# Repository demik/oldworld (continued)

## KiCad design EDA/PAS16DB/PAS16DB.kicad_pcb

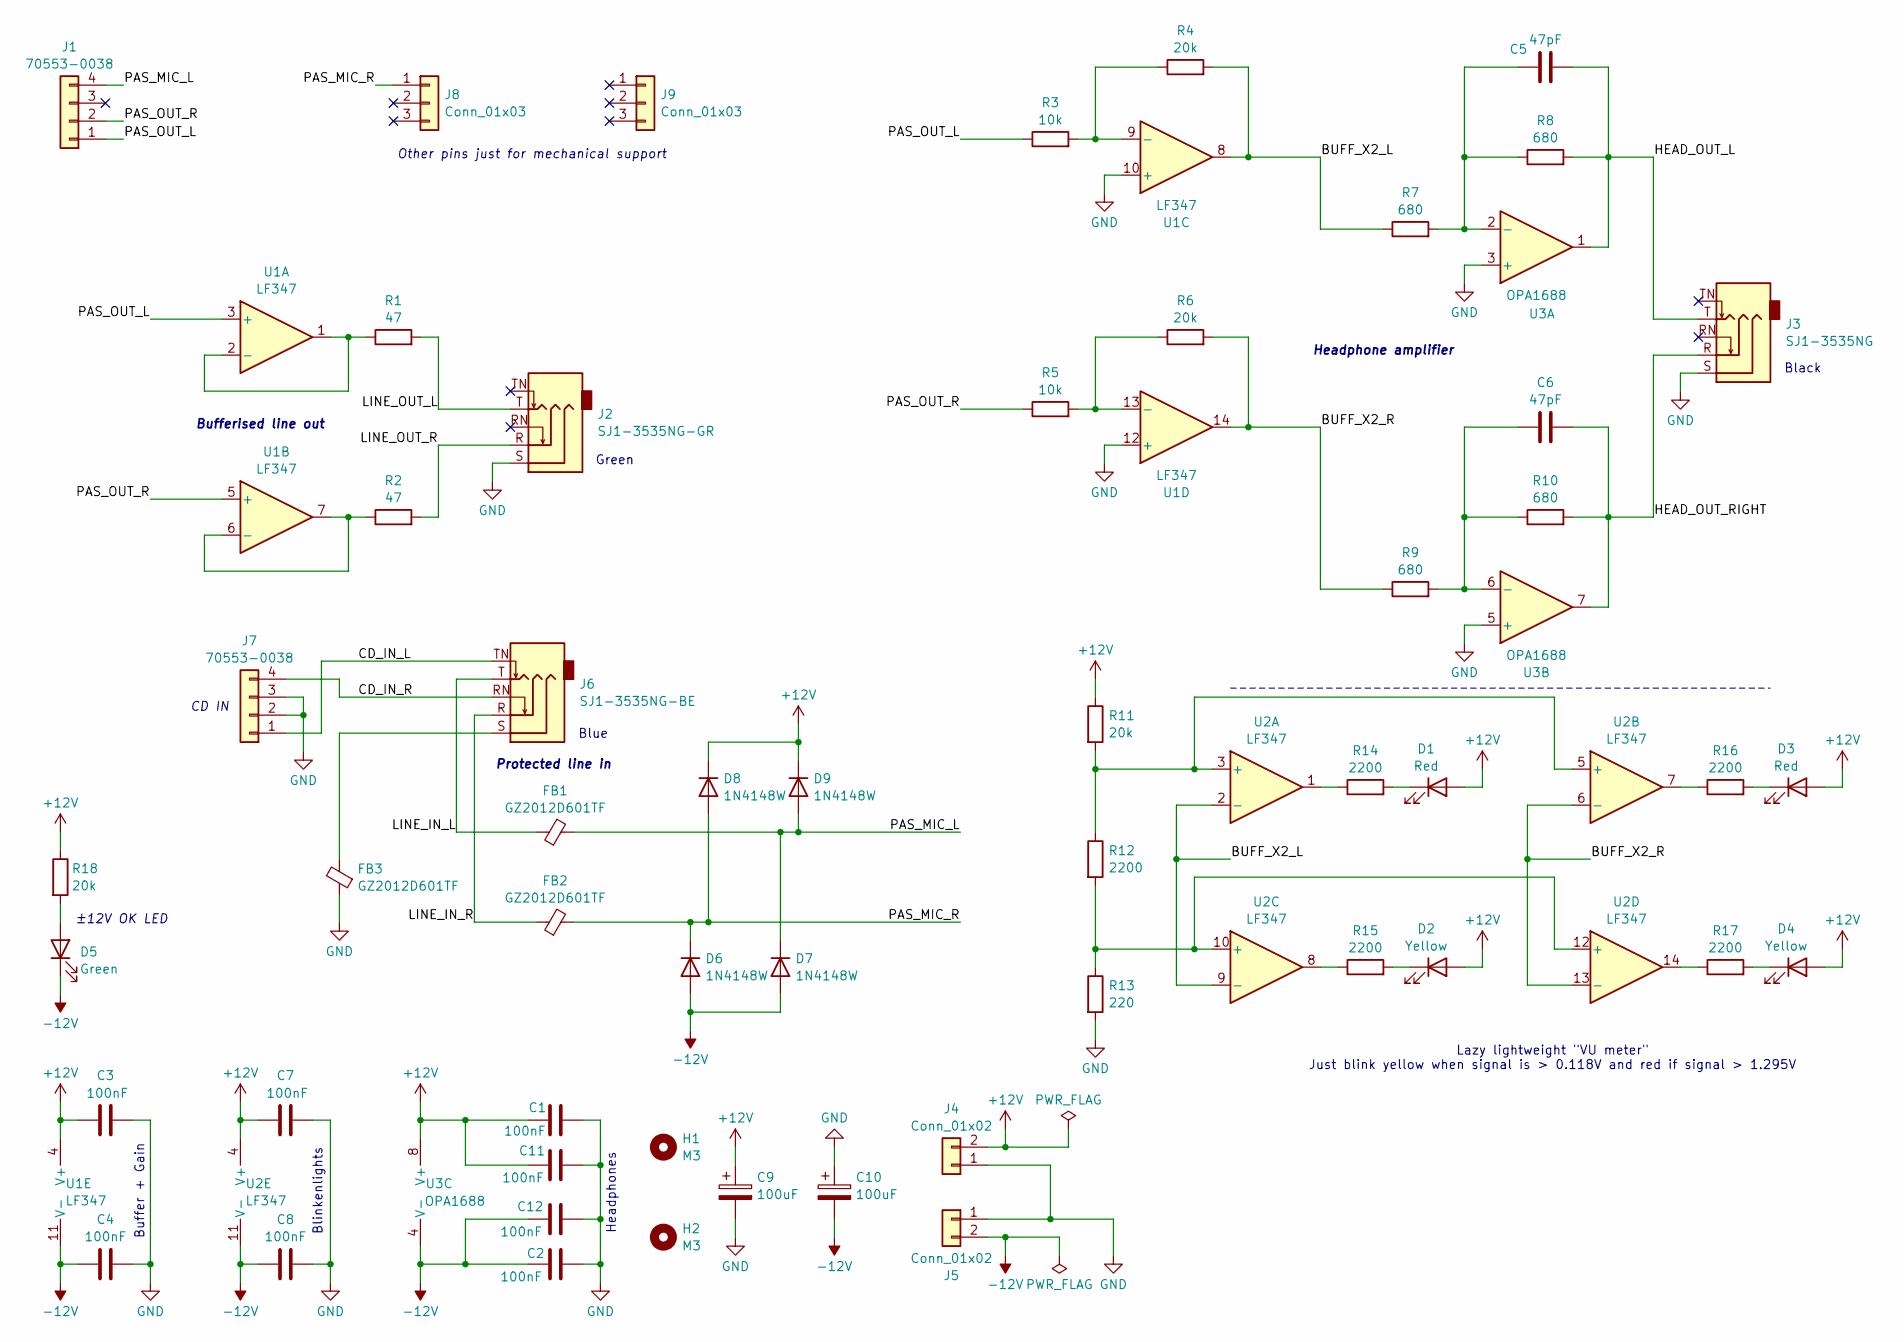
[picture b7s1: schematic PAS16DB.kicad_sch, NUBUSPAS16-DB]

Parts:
C1, C2, C3, C4, C7, C8, C11, C12: 100nF; C_0805_2012Metric; LCSC Part # C49678
C5, C6: 47pF; C_0805_2012Metric; LCSC Part # C14857
C9, C10: 100uF; CP_Axial_L11.0mm_D8.0mm_P15.00mm_Horizontal
D1, D3: Red; LED_0805_2012Metric; LCSC Part # C84256
D2, D4: Yellow; LED_0805_2012Metric; LCSC Part # C2296
D5: Green; LED_0805_2012Metric; LCSC Part # C2297
D6, D7, D8, D9: 1N4148W; D_SOD-123; LCSC Part # C81598
FB1, FB2, FB3: GZ2012D601TF; L_0805_2012Metric; LCSC Part # C1017
H1, H2: M3; MountingHole_3.2mm_M3
J1, J7: 70553-0038; 0705530003; LCSC Part # C564148
J2: SJ1-3535NG-GR; Jack_3.5mm_CUI_SJ1-3535NG_Horizontal; LCSC Part # C4992036
J3: SJ1-3535NG; Jack_3.5mm_CUI_SJ1-3535NG_Horizontal; LCSC Part # C4991610
J4, J5: Conn_01x02; PinHeader_1x02_P2.54mm_Vertical
J6: SJ1-3535NG-BE; Jack_3.5mm_CUI_SJ1-3535NG_Horizontal
J8, J9: Conn_01x03; PinHeader_1x03_P2.54mm_Vertical
R1, R2: 47; R_0805_2012Metric; LCSC Part # C17714
R3, R5: 10k; R_0805_2012Metric; LCSC Part # C17414
R4, R6, R11, R18: 20k; R_0805_2012Metric; LCSC Part # C4328
R7, R8, R9, R10: 680; R_0805_2012Metric; LCSC Part # C17798
R12, R14, R15, R16, R17: 2200; R_0805_2012Metric; LCSC Part # C17520
R13: 220; R_0805_2012Metric; LCSC Part # C17557
U1, U2: LF347; SOIC-14_3.9x8.7mm_P1.27mm; LCSC Part # C283322
U3: OPA1688; SOIC-8_3.9x4.9mm_P1.27mm; LCSC Part # C544851

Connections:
+12V: C1.1, C3.1, C7.1, C9.1, C11.1, D1.2 (A), D2.2 (A), D3.2 (A), D4.2 (A), D8.1 (K), D9.1 (K), J4.2, R11.1, R18.1, U1.4 (V+), U2.4 (V+), U3.8 (V+)
-12V: C2.1, C4.1, C8.1, C10.2, C12.1, D5.1 (K), D6.2 (A), D7.2 (A), J5.2, U1.11 (V-), U2.11 (V-), U3.4 (V-)
/BUFF_X2_L: R4.2, R7.1, U1.8, U2.2 (-), U2.9 (-)
/BUFF_X2_R: R6.2, R9.1, U1.14, U2.6 (-), U2.13 (-)
/CD_IN_L: J6.TN, J7.1
/CD_IN_R: J6.RN, J7.4
/HEAD_OUT_L: C5.2, J3.T, R8.2, U3.1
/HEAD_OUT_RIGHT: C6.2, J3.R, R10.2, U3.7
/LINE_IN_L: FB1.1, J6.T
/LINE_IN_R: FB2.1, J6.R
/LINE_OUT_L: J2.T, R1.2
/LINE_OUT_R: J2.R, R2.2
/PAS_MIC_L: D7.1 (K), D9.2 (A), FB1.2, J1.4
/PAS_MIC_R: D6.1 (K), D8.2 (A), FB2.2, J8.1
/PAS_OUT_L: J1.1, R3.1, U1.3 (+)
/PAS_OUT_R: J1.2, R5.1, U1.5 (+)
GND: C1.2, C2.2, C3.2, C4.2, C7.2, C8.2, C9.2, C10.1, C11.2, C12.2, FB3.1, J2.S, J3.S, J4.1, J5.1, J7.2, J7.3, R13.2, U1.10 (+), U1.12 (+), U3.3 (+), U3.5 (+)
unnamed: D1.1 (K), R14.2
unnamed: D2.1 (K), R15.2
unnamed: D3.1 (K), R16.2
unnamed: D4.1 (K), R17.2
unnamed: D5.2 (A), R18.2
unnamed: FB3.2, J6.S
unnamed: R14.1, U2.1
unnamed: R15.1, U2.8
unnamed: R16.1, U2.7
unnamed: R17.1, U2.14
unnamed: R1.1, U1.1, U1.2 (-)
unnamed: R2.1, U1.6 (-), U1.7
unnamed: R3.2, R4.1, U1.9 (-)
unnamed: R5.2, R6.1, U1.13 (-)
unnamed: R11.2, R12.1, U2.3 (+), U2.5 (+)
unnamed: R12.2, R13.1, U2.10 (+), U2.12 (+)
unnamed: C5.1, R7.2, R8.1, U3.2 (-)
unnamed: C6.1, R9.2, R10.1, U3.6 (-)

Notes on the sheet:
±12V OK LED
Black
Bufferised line out
Other pins just for mechanical support
Headphones
Lazy lightweight "VU meter" Just blink yellow when signal is > 0.118V and red if signal > 1.295V
Headphone amplifier
CD IN
Protected line in
Green
Blinkenlights
Blue
Buffer + Gain

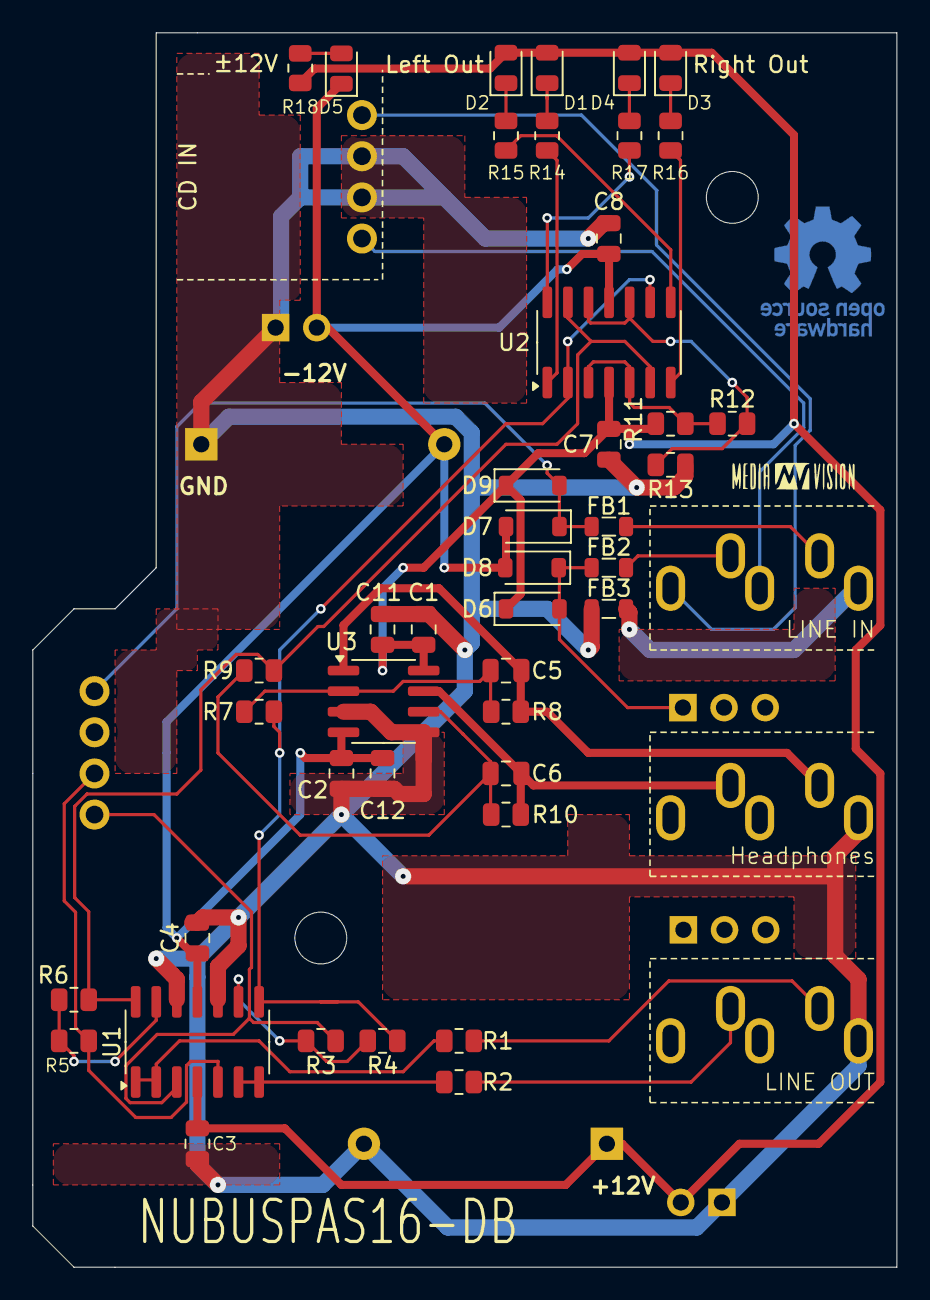
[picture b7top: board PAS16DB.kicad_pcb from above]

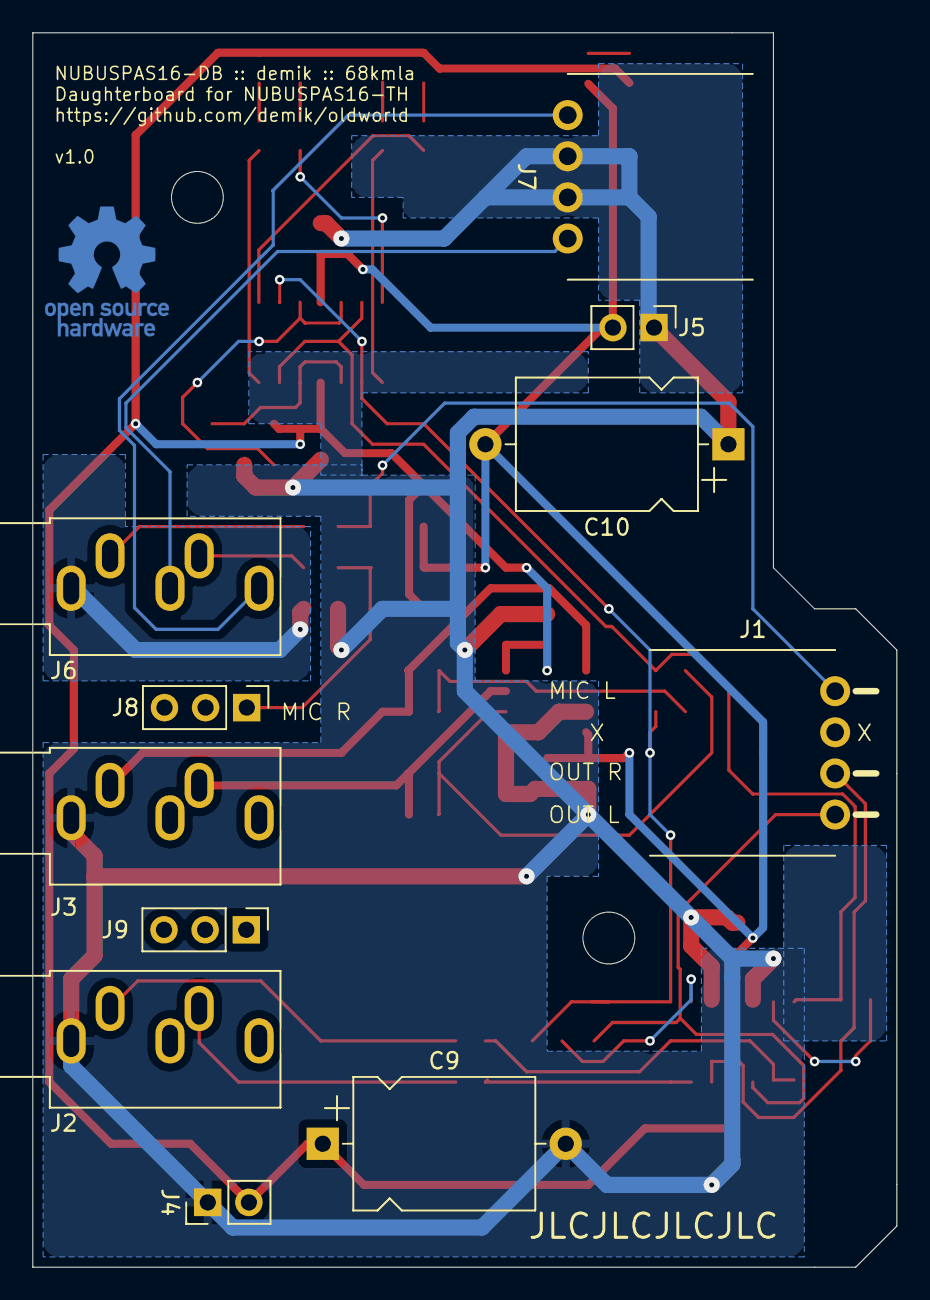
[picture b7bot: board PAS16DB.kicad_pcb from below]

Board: 2 copper layers, 53.3 x 76.2 mm, 56 parts (11 on the bottom side), 35 nets.

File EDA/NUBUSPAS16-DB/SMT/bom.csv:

Designator,Footprint,Quantity,Value,LCSC Part #
C1,0805,1,100nF,<pcbnew.PCB_FIELD; proxy of <Swig Object of type 'PCB_FIELD *' at 0x125257690> >
C10,CP_Axial_L11.0mm_D8.0mm_P15.00mm_Horizontal,1,100uF,<pcbnew.PCB_FIELD; proxy of <Swig Object of type 'PCB_FIELD *' at 0x124cc8b70> >
C11,0805,1,100nF,<pcbnew.PCB_FIELD; proxy of <Swig Object of type 'PCB_FIELD *' at 0x124cc8450> >
C12,0805,1,100nF,<pcbnew.PCB_FIELD; proxy of <Swig Object of type 'PCB_FIELD *' at 0x124cc8180> >
C2,0805,1,100nF,<pcbnew.PCB_FIELD; proxy of <Swig Object of type 'PCB_FIELD *' at 0x124cc8840> >
C3,0805,1,100nF,<pcbnew.PCB_FIELD; proxy of <Swig Object of type 'PCB_FIELD *' at 0x124c71570> >
C4,0805,1,100nF,<pcbnew.PCB_FIELD; proxy of <Swig Object of type 'PCB_FIELD *' at 0x124c71660> >
C5,0805,1,47pF,<pcbnew.PCB_FIELD; proxy of <Swig Object of type 'PCB_FIELD *' at 0x124c71f30> >
C6,0805,1,47pF,<pcbnew.PCB_FIELD; proxy of <Swig Object of type 'PCB_FIELD *' at 0x124c71bd0> >
C7,0805,1,100nF,<pcbnew.PCB_FIELD; proxy of <Swig Object of type 'PCB_FIELD *' at 0x124c71ba0> >
C8,0805,1,100nF,<pcbnew.PCB_FIELD; proxy of <Swig Object of type 'PCB_FIELD *' at 0x124c71a50> >
C9,CP_Axial_L11.0mm_D8.0mm_P15.00mm_Horizontal,1,100uF,<pcbnew.PCB_FIELD; proxy of <Swig Object of type 'PCB_FIELD *' at 0x124c71a20> >
D1,0805,1,Red,<pcbnew.PCB_FIELD; proxy of <Swig Object of type 'PCB_FIELD *' at 0x124c71420> >
D2,0805,1,Yellow,<pcbnew.PCB_FIELD; proxy of <Swig Object of type 'PCB_FIELD *' at 0x124c71b40> >
D3,0805,1,Red,<pcbnew.PCB_FIELD; proxy of <Swig Object of type 'PCB_FIELD *' at 0x124c71630> >
D4,0805,1,Yellow,<pcbnew.PCB_FIELD; proxy of <Swig Object of type 'PCB_FIELD *' at 0x124c71600> >
D5,0805,1,Green,<pcbnew.PCB_FIELD; proxy of <Swig Object of type 'PCB_FIELD *' at 0x124c71c60> >
D6,D_SOD-123,1,1N4148W,<pcbnew.PCB_FIELD; proxy of <Swig Object of type 'PCB_FIELD *' at 0x124c715a0> >
D7,D_SOD-123,1,1N4148W,<pcbnew.PCB_FIELD; proxy of <Swig Object of type 'PCB_FIELD *' at 0x1259c8b40> >
D8,D_SOD-123,1,1N4148W,<pcbnew.PCB_FIELD; proxy of <Swig Object of type 'PCB_FIELD *' at 0x1259c8330> >
D9,D_SOD-123,1,1N4148W,<pcbnew.PCB_FIELD; proxy of <Swig Object of type 'PCB_FIELD *' at 0x1259c8ae0> >
FB1,0805,1,GZ2012D601TF,<pcbnew.PCB_FIELD; proxy of <Swig Object of type 'PCB_FIELD *' at 0x1259c8ab0> >
FB2,0805,1,GZ2012D601TF,<pcbnew.PCB_FIELD; proxy of <Swig Object of type 'PCB_FIELD *' at 0x1259c8c30> >
FB3,0805,1,GZ2012D601TF,<pcbnew.PCB_FIELD; proxy of <Swig Object of type 'PCB_FIELD *' at 0x1259c8c90> >
H1,MountingHole_3.2mm_M3,1,M3,<pcbnew.PCB_FIELD; proxy of <Swig Object of type 'PCB_FIELD *' at 0x1259c83c0> >
H2,MountingHole_3.2mm_M3,1,M3,<pcbnew.PCB_FIELD; proxy of <Swig Object of type 'PCB_FIELD *' at 0x1259c8c00> >
J1,0705530003,1,70553-0038,<pcbnew.PCB_FIELD; proxy of <Swig Object of type 'PCB_FIELD *' at 0x1259c8270> >
J2,Jack_3.5mm_CUI_SJ1-3535NG_Horizontal,1,SJ1-3535NG-GR,<pcbnew.PCB_FIELD; proxy of <Swig Object of type 'PCB_FIELD *' at 0x1259c84b0> >
J3,Jack_3.5mm_CUI_SJ1-3535NG_Horizontal,1,SJ1-3535NG,<pcbnew.PCB_FIELD; proxy of <Swig Object of type 'PCB_FIELD *' at 0x1259c8cf0> >
J4,PinHeader_1x02_P2.54mm_Vertical,1,Conn_01x02,<pcbnew.PCB_FIELD; proxy of <Swig Object of type 'PCB_FIELD *' at 0x1259c8d20> >
J5,PinHeader_1x02_P2.54mm_Vertical,1,Conn_01x02,<pcbnew.PCB_FIELD; proxy of <Swig Object of type 'PCB_FIELD *' at 0x1259c8f00> >
J6,Jack_3.5mm_CUI_SJ1-3535NG_Horizontal,1,SJ1-3535NG-BE,<pcbnew.PCB_FIELD; proxy of <Swig Object of type 'PCB_FIELD *' at 0x1259c8ed0> >
J7,0705530003,1,70553-0038,<pcbnew.PCB_FIELD; proxy of <Swig Object of type 'PCB_FIELD *' at 0x1259c8720> >
J8,PinHeader_1x03_P2.54mm_Vertical,1,Conn_01x03,<pcbnew.PCB_FIELD; proxy of <Swig Object of type 'PCB_FIELD *' at 0x1259c8750> >
J9,PinHeader_1x03_P2.54mm_Vertical,1,Conn_01x03,<pcbnew.PCB_FIELD; proxy of <Swig Object of type 'PCB_FIELD *' at 0x1259c8f30> >
R1,0805,1,47,<pcbnew.PCB_FIELD; proxy of <Swig Object of type 'PCB_FIELD *' at 0x1259c8f60> >
R10,0805,1,680,<pcbnew.PCB_FIELD; proxy of <Swig Object of type 'PCB_FIELD *' at 0x1259c8db0> >
R11,0805,1,20k,<pcbnew.PCB_FIELD; proxy of <Swig Object of type 'PCB_FIELD *' at 0x124ea4840> >
R12,0805,1,2200,<pcbnew.PCB_FIELD; proxy of <Swig Object of type 'PCB_FIELD *' at 0x124ea4bd0> >
R13,0805,1,220,<pcbnew.PCB_FIELD; proxy of <Swig Object of type 'PCB_FIELD *' at 0x124ea4990> >
R14,0805,1,2200,<pcbnew.PCB_FIELD; proxy of <Swig Object of type 'PCB_FIELD *' at 0x124ea4630> >
R15,0805,1,2200,<pcbnew.PCB_FIELD; proxy of <Swig Object of type 'PCB_FIELD *' at 0x124ea4600> >
R16,0805,1,2200,<pcbnew.PCB_FIELD; proxy of <Swig Object of type 'PCB_FIELD *' at 0x124ea4420> >
R17,0805,1,2200,<pcbnew.PCB_FIELD; proxy of <Swig Object of type 'PCB_FIELD *' at 0x124ea43f0> >
R18,0805,1,20k,<pcbnew.PCB_FIELD; proxy of <Swig Object of type 'PCB_FIELD *' at 0x124ea4720> >
R2,0805,1,47,<pcbnew.PCB_FIELD; proxy of <Swig Object of type 'PCB_FIELD *' at 0x124ea4750> >
R3,0805,1,10k,<pcbnew.PCB_FIELD; proxy of <Swig Object of type 'PCB_FIELD *' at 0x124ea46f0> >
R4,0805,1,20k,<pcbnew.PCB_FIELD; proxy of <Swig Object of type 'PCB_FIELD *' at 0x124ea47e0> >
R5,0805,1,10k,<pcbnew.PCB_FIELD; proxy of <Swig Object of type 'PCB_FIELD *' at 0x124ea4de0> >
R6,0805,1,20k,<pcbnew.PCB_FIELD; proxy of <Swig Object of type 'PCB_FIELD *' at 0x124ea4300> >
R7,0805,1,680,<pcbnew.PCB_FIELD; proxy of <Swig Object of type 'PCB_FIELD *' at 0x124ea4db0> >
R8,0805,1,680,<pcbnew.PCB_FIELD; proxy of <Swig Object of type 'PCB_FIELD *' at 0x124ea4e10> >
R9,0805,1,680,<pcbnew.PCB_FIELD; proxy of <Swig Object of type 'PCB_FIELD *' at 0x124ea42d0> >
U1,SOIC-14_3.9x8.7mm_P1.27mm,1,LF347,<pcbnew.PCB_FIELD; proxy of <Swig Object of type 'PCB_FIELD *' at 0x124ea41e0> >
U2,SOIC-14_3.9x8.7mm_P1.27mm,1,LF347,<pcbnew.PCB_FIELD; proxy of <Swig Object of type 'PCB_FIELD *' at 0x124ea4b10> >
U3,SOIC-8_3.9x4.9mm_P1.27mm,1,OPA1688,<pcbnew.PCB_FIELD; proxy of <Swig Object of type 'PCB_FIELD *' at 0x124ea4b40> >

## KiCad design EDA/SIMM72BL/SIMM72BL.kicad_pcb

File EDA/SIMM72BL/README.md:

# SIMM72BL

SIMM 72 BlinkenLights

This is an interposer 72 pins memory SIMM tool for troubleshooting purposes.
It was created to debug stuck lines on a memory controller, but you can probably use it to debug some bad memory chips as well

The top of the board has pads for probing, and you can solder an inline SIMM socket here as well.
Each line has its on activity LED

### Usage

Don't break your existing SIMM socket

### Building

PCB thickness should be 1.2 milimeters 

This has been designed to use only basic components, and can be build by your favorite PCBA service.
The corrected bom + position files for JLCPCB assembly are avaiable inside the [SMT](https://github.com/demik/oldworld/tree/master/EDA/SIMM72BL/SMT) subdirectory. You will still need to buy the SIMM connector if you want to support an inline memory module

Full BOM if you want to build it from scratch:

| Reference(s)          | Value      | Quantity | Notes                                  | Part number           |
|-----------------------|------------|----------|----------------------------------------|-----------------------|
| C1 to C9, C12, C13    | 100nF      | 11       | X7R 0402 Multilayer Ceramic Capacitors | SEM CL05B104KO5NNNC   |
| C10, C11              | 10uF       | 2        | 1206 Tantalum Capacitors               | AVX TAJA106K016RNJ    |
| D1 to 32              | Emerald    | 32       | 0805 Light Emitting Diodes             | Hubei KT-0805G        |
| D33 to D52            | Yellow     | 20       | 0805 Light Emitting Diodes             | Hubei KT-0805Y        |
| D53                   | White      | 1        | 0805 Light Emitting Diodes             | Hubei KT-0805W        |
| D54                   | Red        | 1        | 0805 Light Emitting Diodes             | Hubei KT-0805R        |
| R1 to R32, R53        | 3.3kΩ      | 33       | 0402 Chip Resistor 62.5mW              | Uni 0402WGF3301TCE    |
| R33 to R52, R54, R55  | 510Ω       | 22       | 0402 Chip Resistor 62.5mW              | Uni 0402WGF5100TCE    |
| U2 to U10             | 74HC14     | 9        | SOIC-14 6 Schmitt Trigger inverter     | Nextperia 74HC14D     |
| Connector             | SIMM72     | 1        | Vertical SIMM Connectors 72 connector  | TE 5822021-4          |

The SIMM connector pin spacing doesn't really match the PCB thickness. You will want to solder the back first with the pins flat, then bent the pins slightly on the front side, and use a little bit more solder than usual

The gerbers files are downloadable [here](https://github.com/demik/oldworld/releases/download/SIMM72BL%2Fv1.2.0/SIMM72BL_1.2.zip)

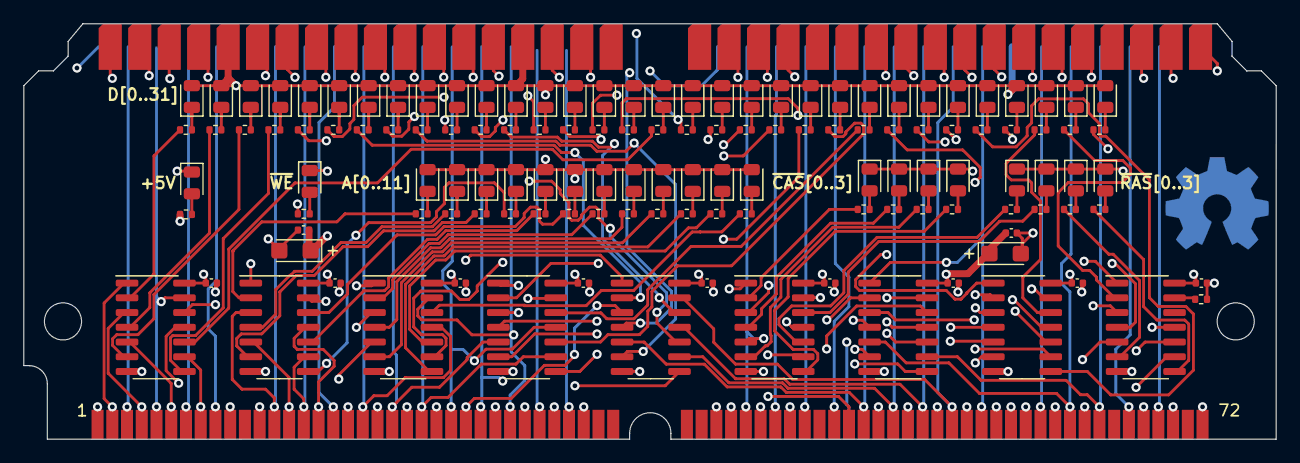
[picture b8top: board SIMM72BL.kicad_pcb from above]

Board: 4 copper layers, 108.0 x 35.8 mm, 133 parts (0 on the bottom side), 167 nets.

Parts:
C1, C2, C3, C4, C5, C6, C7, C8, C9, C12, C13: 100nF; C_0402_1005Metric
C10, C11: 10uF; CP_EIA-3216-10_Kemet-I
D1, D2, D3, D4, D5, D6, D7, D8, D9, D10, D11, D12, D13, D14, D15, D16, D17, D18, D19, D20, D21, D22, D23, D24, D25, D26, D27, D28, D29, D30, D31, D32: GREEN; D_0805_2012Metric
D33, D34, D35, D36, D37, D38, D39, D40, D41, D42, D43, D44, D45, D46, D47, D48, D49, D50, D51, D52: YELLOW; D_0805_2012Metric
D53: WHITE; D_0805_2012Metric
D54: RED; D_0805_2012Metric
J1: 5822021-4; 5822021-4_EoB
R1, R2, R3, R4, R5, R6, R7, R8, R9, R10, R11, R12, R13, R14, R15, R16, R17, R18, R19, R20, R21, R22, R23, R24, R25, R26, R27, R28, R29, R30, R31, R32, R53: 3kΩ; R_0402_1005Metric
R33, R34, R35, R36, R37, R38, R39, R40, R41, R42, R43, R44, R45, R46, R47, R48, R49, R50, R51, R52, R54, R55: 510Ω; R_0402_1005Metric
U1: SIMM-72
U2, U3, U4, U5, U6, U7, U8, U9, U10: 74HC14; SOIC-14_3.9x8.7mm_P1.27mm

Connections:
+5V: C1.1, C2.1, C3.1, C4.1, C5.1, C6.1, C7.1, C8.1, C9.1, C10.1, C11.1, C12.1, C13.1, D1.2 (A), D2.2 (A), D3.2 (A), D4.2 (A), D5.2 (A), D6.2 (A), D7.2 (A), D8.2 (A), D9.2 (A), D10.2 (A), D11.2 (A), D12.2 (A), D13.2 (A), D14.2 (A), D15.2 (A), D16.2 (A), D17.2 (A), D18.2 (A), D19.2 (A), D20.2 (A), D21.2 (A), D22.2 (A), D23.2 (A), D24.2 (A), D25.2 (A), D26.2 (A), D27.2 (A), D28.2 (A), D29.2 (A), D30.2 (A), D31.2 (A), D32.2 (A), D33.2 (A), D34.2 (A), D35.2 (A), D36.2 (A), D37.2 (A), D38.2 (A), D39.2 (A), D40.2 (A), D41.2 (A), D42.2 (A), D43.2 (A), D44.2 (A), J1.10, J1.30, J1.59, R53.1, U1.10 (+5V), U1.30 (+5V), U1.59 (+5V), U2.14 (VCC), U3.14 (VCC), U4.14 (VCC), U5.14 (VCC), U6.14 (VCC), U7.14 (VCC), U8.14 (VCC), U9.14 (VCC), U10.14 (VCC)
/A0: J1.12, U1.12 (A0), U8.1
/A1: J1.13, U1.13 (A1), U8.3
/A2: J1.14, U1.14 (A2), U8.5
/A3: J1.15, U1.15 (A3), U8.9
/A4: J1.16, U1.16 (A4), U8.11
/A5: J1.17, U1.17 (A5), U8.13
/A6: J1.18, U1.18 (A6), U9.1
/A7: J1.28, U1.28 (A7), U9.3
/A8: J1.31, U1.31 (A8), U9.5
/A9: J1.32, U1.32 (A9), U9.9
/A10: J1.19, U1.19 (A10), U9.11
/A11: J1.29, U1.29 (A11), U9.13
/PD1: J1.67, U1.67 (PD1)
/PD2: J1.68, U1.68 (PD2)
/PD3: J1.69, U1.69 (PD3)
/PD4: J1.70, U1.70 (PD4)
/~CAS0: J1.40, U1.40 (~CAS0), U10.1
/~CAS1: J1.43, U1.43 (~CAS1), U10.3
/~CAS2: J1.41, U1.41 (~CAS2), U10.5
/~CAS3: J1.42, U1.42 (~CAS3), U10.9
/~RAS0: J1.44, U1.44 (~RAS0), U10.11
/~RAS1: J1.45, U1.45 (~RAS1), U10.13
/~RAS2: J1.34, U1.34 (~RAS2), U7.5
/~RAS3: J1.33, U1.33 (~RAS3), U7.9
/~WE: J1.47, U1.47 (~WE), U7.11
DQ0: J1.2, U1.2 (DQ0), U2.1
DQ1: J1.4, U1.4 (DQ1), U2.3
DQ2: J1.6, U1.6 (DQ2), U2.5
DQ3: J1.8, U1.8 (DQ3), U2.9
DQ4: J1.20, U1.20 (DQ4), U4.11
DQ5: J1.22, U1.22 (DQ5), U4.13
DQ6: J1.24, U1.24 (DQ6), U3.1
DQ7: J1.26, U1.26 (DQ7), U3.3
DQ8: J1.49, U1.49 (DQ8), U3.5
DQ9: J1.51, U1.51 (DQ9), U3.9
DQ10: J1.53, U1.53 (DQ10), U3.11
DQ11: J1.55, U1.55 (DQ11), U3.13
DQ12: J1.57, U1.57 (DQ12), U4.1
DQ13: J1.61, U1.61 (DQ13), U4.3
DQ14: J1.63, U1.63 (DQ14), U4.5
DQ15: J1.65, U1.65 (DQ15), U4.9
DQ16: J1.3, U1.3 (DQ16), U2.11
DQ17: J1.5, U1.5 (DQ17), U2.13
DQ18: J1.7, U1.7 (DQ18), U5.1
DQ19: J1.9, U1.9 (DQ19), U5.3
DQ20: J1.21, U1.21 (DQ20), U5.5
DQ21: J1.23, U1.23 (DQ21), U5.9
DQ22: J1.25, U1.25 (DQ22), U5.11
DQ23: J1.27, U1.27 (DQ23), U5.13
DQ24: J1.50, U1.50 (DQ24), U6.1
DQ25: J1.52, U1.52 (DQ25), U6.3
DQ26: J1.54, U1.54 (DQ26), U6.5
DQ27: J1.56, U1.56 (DQ27), U6.9
DQ28: J1.58, U1.58 (DQ28), U6.11
DQ29: J1.60, U1.60 (DQ29), U6.13
DQ30: J1.62, U1.62 (DQ30), U7.1
DQ31: J1.64, U1.64 (DQ31), U7.3
GND: C1.2, C2.2, C3.2, C4.2, C5.2, C6.2, C7.2, C8.2, C9.2, C10.2, C11.2, C12.2, C13.2, D45.1 (K), D46.1 (K), D47.1 (K), D48.1 (K), D49.1 (K), D50.1 (K), D51.1 (K), D52.1 (K), D53.1 (K), D54.1 (K), J1.1, J1.39, J1.72, R55.1, U1.1 (GND), U1.39 (GND), U1.72 (GND), U2.7 (GND), U3.7 (GND), U4.7 (GND), U5.7 (GND), U6.7 (GND), U7.7 (GND), U8.7 (GND), U9.7 (GND), U10.7 (GND)
unnamed: D1.1 (K), R1.2
unnamed: D2.1 (K), R2.2
unnamed: D3.1 (K), R3.2
unnamed: D4.1 (K), R4.2
unnamed: D5.1 (K), R5.2
unnamed: D6.1 (K), R6.2
unnamed: D7.1 (K), R7.2
unnamed: D8.1 (K), R8.2
unnamed: D9.1 (K), R9.2
unnamed: D10.1 (K), R10.2
unnamed: D11.1 (K), R11.2
unnamed: D12.1 (K), R12.2
unnamed: D13.1 (K), R13.2
unnamed: D14.1 (K), R14.2
unnamed: D15.1 (K), R15.2
unnamed: D16.1 (K), R16.2
unnamed: D17.1 (K), R17.2
unnamed: D18.1 (K), R18.2
unnamed: D19.1 (K), R19.2
unnamed: D20.1 (K), R20.2
unnamed: D21.1 (K), R21.2
unnamed: D22.1 (K), R22.2
unnamed: D23.1 (K), R23.2
unnamed: D24.1 (K), R24.2
unnamed: D25.1 (K), R25.2
unnamed: D26.1 (K), R26.2
unnamed: D27.1 (K), R27.2
unnamed: D28.1 (K), R28.2
unnamed: D29.1 (K), R29.2
unnamed: D30.1 (K), R30.2
unnamed: D31.1 (K), R31.2
unnamed: D32.1 (K), R32.2
unnamed: D33.1 (K), R33.2
unnamed: D34.1 (K), R34.2
unnamed: D35.1 (K), R35.2
unnamed: D36.1 (K), R36.2
unnamed: D37.1 (K), R37.2
unnamed: D38.1 (K), R38.2
unnamed: D39.1 (K), R39.2
unnamed: D40.1 (K), R40.2
unnamed: D41.1 (K), R41.2
unnamed: D42.1 (K), R42.2
unnamed: D43.1 (K), R43.2
unnamed: D44.1 (K), R44.2
unnamed: D45.2 (A), R45.2
unnamed: D46.2 (A), R46.2
unnamed: D47.2 (A), R47.2
unnamed: D48.2 (A), R48.2
unnamed: D49.2 (A), R49.2
unnamed: D50.2 (A), R50.2
unnamed: D51.2 (A), R51.2
unnamed: D52.2 (A), R52.2
unnamed: D53.2 (A), R53.2
unnamed: D54.2 (A), R54.2
unnamed: R1.1, U2.2
unnamed: R2.1, U2.4
unnamed: R3.1, U2.6
unnamed: R4.1, U2.8
unnamed: R5.1, U4.10
unnamed: R6.1, U4.12
unnamed: R7.1, U3.2
unnamed: R8.1, U3.4
unnamed: R9.1, U3.6
unnamed: R10.1, U3.8
unnamed: R11.1, U3.10
unnamed: R12.1, U3.12
unnamed: R13.1, U4.2
unnamed: R14.1, U4.4
unnamed: R15.1, U4.6
unnamed: R16.1, U4.8
unnamed: R17.1, U2.10
unnamed: R18.1, U2.12
unnamed: R19.1, U5.2
unnamed: R20.1, U5.4
unnamed: R21.1, U5.6
unnamed: R22.1, U5.8
unnamed: R23.1, U5.10
unnamed: R24.1, U5.12
unnamed: R25.1, U6.2
unnamed: R26.1, U6.4
unnamed: R27.1, U6.6
unnamed: R28.1, U6.8
unnamed: R29.1, U6.10
unnamed: R30.1, U6.12
unnamed: R31.1, U7.2
unnamed: R32.1, U7.4
unnamed: R33.1, U8.2
unnamed: R34.1, U8.4
unnamed: R35.1, U8.6
unnamed: R36.1, U8.8
unnamed: R37.1, U8.10
unnamed: R38.1, U8.12
unnamed: R39.1, U9.2
unnamed: R40.1, U9.4
unnamed: R41.1, U9.6
unnamed: R42.1, U9.8
unnamed: R43.1, U9.10
unnamed: R44.1, U9.12
unnamed: R45.1, U10.2
unnamed: R46.1, U10.4
unnamed: R47.1, U10.6
unnamed: R48.1, U10.8
unnamed: R49.1, U10.10
unnamed: R50.1, U10.12
unnamed: R51.1, U7.6
unnamed: R52.1, U7.8
unnamed: R54.1, U7.10
unnamed: R55.2, U7.13

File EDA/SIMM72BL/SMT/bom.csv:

Designator,Footprint,Quantity,Value,LCSC Part #
"C1, C12, C13, C2, C3, C4, C5, C6, C7, C8, C9",0402,11,100nF,C1525
"C10, C11",A3216,2,10uF,C7171
"D1, D10, D11, D12, D13, D14, D15, D16, D17, D18, D19, D2, D20, D21, D22, D23, D24, D25, D26, D27, D28, D29, D3, D30, D31, D32, D4, D5, D6, D7, D8, D9",0805,32,GREEN,C2297
"D33, D34, D35, D36, D37, D38, D39, D40, D41, D42, D43, D44, D45, D46, D47, D48, D49, D50, D51, D52",0805,20,YELLOW,C2296
D53,0805,1,WHITE,C34499
D54,0805,1,RED,C84256
"R1, R10, R11, R12, R13, R14, R15, R16, R17, R18, R19, R2, R20, R21, R22, R23, R24, R25, R26, R27, R28, R29, R3, R30, R31, R32, R4, R5, R53, R6, R7, R8, R9",0402,33,3kΩ,C25890
"R33, R34, R35, R36, R37, R38, R39, R40, R41, R42, R43, R44, R45, R46, R47, R48, R49, R50, R51, R52, R54, R55",0402,22,510Ω,C25123
"U10, U2, U3, U4, U5, U6, U7, U8, U9",SOIC-14_3.9x8.7mm_P1.27mm,9,74HC14,C5605

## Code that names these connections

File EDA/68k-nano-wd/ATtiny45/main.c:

/*
 * ATTiny45 Supervisor and Clock Generator
 * ========================================
 *
 * Features:
 * - Pulse Supervisor: Monitors incoming pulses on PB0, activates LED (PB2) on timeout
 * - Clock Generator: Outputs 10Hz square wave on PB1 (enable/disable via switch)
 * - Clock Enable: Switch on PB3 controls clock output
 * - Clock Status: LED on PB4 indicates clock enable state
 * - Hardware Reset: /RESET signal on PB5 resets entire system
 *
 * Pin Assignment:
 * ---------------
 * - PB0: Pulse input (with pin change interrupt)
 * - PB1: 10Hz clock output (Timer1 OC1A)
 * - PB2: Supervisor LED output (active low)
 * - PB3: Clock enable switch input (active low with pull-up)
 * - PB4: Clock status LED output (active low)
 * - PB5: /RESET input (hardware reset, active low)
 *
 * Reset Behavior:
 * ---------------
 * When /RESET (PB5) is pulled low, the microcontroller performs a hardware reset:
 * - All registers and timers are reset to default values
 * - All interrupts are disabled
 * - All I/O pins return to input state
 * - Program execution restarts from main()
 * - Supervisor becomes idle and starts monitoring from beginning
 *
 * Programming with TL866/T48 (minipro):
 * -------------------------------------
 * Build:           make
 * Flash:           make minipro-flash
 * Test:            make minipro-test
 * Read fuses:      make minipro-read-fuses
 * Write fuses:     make minipro-write-fuses (edit fuses.conf first)
 *
 * Manual minipro commands:
 *   minipro -p ATTINY45 -w attiny45_supervisor.hex        # Flash firmware
 *   minipro -p ATTINY45 -r backup.hex                     # Read flash
 *   minipro -p ATTINY45 -c config -r                      # Read fuses
 *   minipro -p ATTINY45 -c config -w fuses.conf           # Write fuses
 *   minipro -p ATTINY45 -E                                # Erase chip
 *
 * Fuse Settings (8MHz internal oscillator):
 * -----------------------------------------
 * LFUSE = 0xE2  (8MHz internal RC, no prescaler)
 * HFUSE = 0xDF  (RESET enabled, SPI enabled, BOD disabled)
 * EFUSE = 0xFF  (Self-programming disabled)
 *
 * WARNING: Never program RSTDISBL fuse (HFUSE bit 7) or SPIEN fuse (HFUSE bit 5)
 *          unless you have high-voltage programming capability!
 */

#include <avr/io.h>
#include <avr/interrupt.h>
#include <stdint.h>

// Configuration
#ifndef F_CPU
#define F_CPU 8000000UL  // 8MHz internal oscillator
#endif

// Pin definitions
#define PIN_PULSE_INPUT      PB0
#define PIN_CLOCK_OUTPUT     PB1
#define PIN_SUPERVISOR_LED   PB2
#define PIN_CLOCK_ENABLE_SW  PB3
#define PIN_CLOCK_STATUS_LED PB4

// Timeout configuration
// Timer0 with 1024 prescaler @ 8MHz: overflow every ~32.8ms
// 33 overflows = ~1.08 seconds
#define TIMEOUT_THRESHOLD 33

// Global state
volatile uint8_t timeout_counter = 0;
volatile uint8_t last_pinb = 0;

/*
 * Pin Change Interrupt - Pulse Input Monitor
 * Triggers on any edge change on PB0
 */
ISR(PCINT0_vect)
{
    uint8_t current_pinb = PINB;

    // Detect falling edge on PB0 (pulse received)
    if ((last_pinb & (1 << PIN_PULSE_INPUT)) &&
        !(current_pinb & (1 << PIN_PULSE_INPUT))) {

        // Valid pulse detected - reset timeout counter
        timeout_counter = 0;

        // Clear LED (inactive = high)
        PORTB |= (1 << PIN_SUPERVISOR_LED);
    }

    last_pinb = current_pinb;
}

/*
 * Timer0 Overflow Interrupt - Timeout Monitor
 * Overflows approximately every 32.8ms at 8MHz with 1024 prescaler
 */
ISR(TIM0_OVF_vect)
{
    timeout_counter++;

    // Check if timeout threshold exceeded
    if (timeout_counter >= TIMEOUT_THRESHOLD) {
        // Timeout occurred - activate LED (active low)
        PORTB &= ~(1 << PIN_SUPERVISOR_LED);

        // Cap counter to prevent overflow
        timeout_counter = TIMEOUT_THRESHOLD;
    }
}

/*
 * Initialize GPIO pins
 */
static void init_gpio(void)
{
    // Set pin directions:
    // Outputs: PB1 (clock), PB2 (supervisor LED), PB4 (clock status LED)
    // Inputs: PB0 (pulse), PB3 (clock enable switch)
    DDRB = (1 << PIN_CLOCK_OUTPUT) | (1 << PIN_SUPERVISOR_LED) | (1 << PIN_CLOCK_STATUS_LED);

    // Configure initial states:
    // - PB0: Enable pull-up resistor
    // - PB2: Supervisor LED off (high = inactive)
    // - PB3: Enable pull-up resistor for switch
    // - PB4: Clock status LED off (high = inactive)
    PORTB = (1 << PIN_PULSE_INPUT) | (1 << PIN_SUPERVISOR_LED) |
            (1 << PIN_CLOCK_ENABLE_SW) | (1 << PIN_CLOCK_STATUS_LED);

    // Initialize last pin state
    last_pinb = PINB;
}

/*
 * Initialize Timer1 for 10Hz clock generation
 * Uses CTC mode with toggle output on OC1A (PB1)
 */
static void init_timer1(void)
{
    // Timer1 configuration:
    // - CTC1: Clear Timer on Compare match mode
    // - COM1A0: Toggle OC1A (PB1) on compare match
    // - CS13, CS12, CS10: Prescaler = 1024
    // Formula: f_out = F_CPU / (2 * prescaler * (OCR1A + 1))
    // For 10Hz: OCR1A = F_CPU / (2 * 1024 * 10) - 1 = 8000000 / 20480 - 1 ≈ 389.6 → 390
    // Actual: 8000000 / (2 * 1024 * 391) = 9.99Hz

    TCCR1 = (1 << CTC1) |           // CTC mode
            (1 << COM1A0) |         // Toggle OC1A on compare match
            (1 << CS13) | (1 << CS12) | (1 << CS10); // Prescaler 1024

    // Set compare value for ~10Hz
    OCR1A = 390;
    OCR1C = 390;  // TOP value for CTC mode
}

/*
 * Initialize Timer0 for supervisor timeout
 * Generates overflow interrupts for timeout detection
 */
static void init_timer0(void)
{
    // Timer0 configuration:
    // - CS02, CS00: Prescaler = 1024
    // Overflow period = 256 * 1024 / F_CPU = 256 * 1024 / 8000000 ≈ 32.8ms

    TCCR0B = (1 << CS02) | (1 << CS00);  // Prescaler 1024

    // Enable Timer0 overflow interrupt
    TIMSK |= (1 << TOIE0);
}

/*
 * Initialize pin change interrupt for pulse detection
 */
static void init_pin_change_interrupt(void)
{
    // Enable pin change interrupt on PCINT0 (PB0)
    PCMSK |= (1 << PCINT0);

    // Enable pin change interrupts
    GIMSK |= (1 << PCIE);
}

int main(void)
{
    // Initialize all subsystems
    init_gpio();
    init_timer1();      // Clock generator
    init_timer0();      // Timeout monitor
    init_pin_change_interrupt();  // Pulse detector

    // Enable global interrupts
    sei();

    // Main loop - monitor clock enable switch
    while (1) {
        // Read clock enable switch state (active low)
        uint8_t clock_enabled = !(PINB & (1 << PIN_CLOCK_ENABLE_SW));

        if (clock_enabled) {
            // Enable clock output by connecting OC1A to PB1
            TCCR1 |= (1 << COM1A0);
            // Turn on clock status LED (active low)
            PORTB &= ~(1 << PIN_CLOCK_STATUS_LED);
        } else {
            // Disable clock output by disconnecting OC1A from PB1
            TCCR1 &= ~(1 << COM1A0);
            // Force clock output low when disabled
            PORTB &= ~(1 << PIN_CLOCK_OUTPUT);
            // Turn off clock status LED
            PORTB |= (1 << PIN_CLOCK_STATUS_LED);
        }

        // Small delay to debounce switch (optional)
        // Could also use sleep mode here for power savings
    }

    return 0;
}

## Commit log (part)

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2020-05-06 added library for PDS Slot
2020-05-06 initial HPV riser layout
2020-05-06 Connector_Apple lib update + HPV Riser connections
2020-05-07 PCB Routing done
2020-05-07 HPV Riser render
2020-05-07 HPV PCB routing session
2020-05-07 added Apple Logo in lib
2020-05-08 added datasheets from VRAM & PCI connector
2020-05-08 added PCB Footprint and updated lib for SIMM-68
2020-05-09 Added SIMM-30 footprint
2020-05-11 added SIMM-30 to library
2020-06-05 increased EDAC_302-182-520-900 holes from 0.2 to 0.6
2020-09-05 HPV Riser Rev 1.2: Routing and PCB Edge fixes
2020-09-05 finished schema for V52C8128 256k VRAM stick
2020-12-27 added ROMs for 512ke and StyleWriter II
2021-01-03 added Mac Plus ROM socket to KiKad lib
2021-01-04 added missing DIP-28 Piggy connector
2021-01-05 MacSnap SCSI v0.5
2021-01-08 added 3D JPEG
2021-01-10 added resistor networks + TMPWR
2021-01-12 added active SCSI termination to schema
2021-01-15 removed a few vias and router resistor packs. Moves Z53C80 further down
2021-01-19 added 68030FE to library
2021-02-01 added Quantum ProDrive ELS 27C512 ROM
2021-03-02 added some NuBus ROMs
2021-03-04 added Apple Serial NB ROMs + RasterOps & Radius GPUs
2021-03-10 added Netlist and PDF output for SRAM Memory
2021-03-10 added project name and orther informations
2021-04-29 cleaned old VRAM RE (another community member got this)
2021-05-20 SE/30 Video ROM
2021-07-13 added Formac ProNitron80.21 ROM
2021-11-25 Added DB19 male connector
2021-11-26 added DB19_IDC20 adapter for TashTwenty Mini
2021-11-27 added Formac ProGraph II ROM (thanks Bolle)
2021-11-28 renamed adapter
2021-11-29 added TashTwenty Tiny
2021-11-29 rename ProGraph ROM file
2021-11-29 misc tiding (resistors, led, etc…)
2021-11-29 added project URLs
2021-11-29 added PB5xx Power adapter
2021-11-29 added PB5xx floppy adapter
2021-11-30 fixed DRC errors
2021-11-30 added build order on silkscreen
2021-12-01 mix fixes
2021-12-08 added PAL16 ZIF adapter for reversing stuff
2021-12-08 minor fixes for production
2021-12-13 added Formac ProNitron GA2 ROM
2021-12-15 PB5xx Floppy adapter V.1.1: changed connector + power LED
2021-12-29 added missing PIC16F1825 lib file
2022-01-03 added Formac ProNitron GA19 V18
2022-01-31 aligned hole with support
2022-03-17 Removed TashTwenty Tiny. It's going on https://github.com/lampmerchant/tashtwenty
2022-03-18 moved DB19_IDC20 to tashtwenty repository
2022-04-05 added Piggy footprints for DIP16 and DIP20
2022-04-08 added Formac PDS DeclROM
2022-04-15 misc powerbook connector update
2022-06-09 added Apple TwinTurbo128MA ROM
2023-07-13 PB5xx_ATXCPU: add power LED + upgrade KiKad v7
2023-07-13 PB5xx_ATXCPU: add files for SMT assembly
2023-08-12 PAL16R LART: v1.0.0
2023-08-12 added README.md for PAL16R_LART
2023-08-12 Fix image link in README.md
2023-08-18 Fixed typos in README.md
2023-09-10 Design68: initial release
2023-09-11 added README for Design68
2023-09-11 Update README.md
    Fixed LEDs count
2023-09-11 Update README.md
    Fixed typos
2023-09-12 Update README.md
    Way better README. Add image and elevator pitch
2023-09-13 Update README.md
    Added tested Keycap sets
2023-09-13 Update README.md
    Fixed switch value
2023-09-14 Preparing for ANSI, cleaning
2023-09-14 ANSI PCB 1.0 released
2023-09-17 updated maun README
2023-09-17 fixed links
2023-09-21 MacSnap SCSI pre-2.0 cleaning
2024-01-26 Converted library to new format + added SIMM 72 footprint + symbol
2024-02-14 ADBDB: v1.1 initial release
2024-02-15 added ADBDB picture
2024-02-15 added missing file
2024-02-16 added missing files for Design68 kikad projects
2024-02-16 exclude production subfolders
2024-02-16 ADBDB final touches
2024-02-16 Updated main EDA readme
2024-02-16 minor fixes
2024-02-18 SIMM72BL v1.1: initial public release
2024-02-18 reduced image size
2024-02-18 fixed typos
2024-03-28 PAS16DB v1.0 release
2024-03-30 NUBUSPAS16-DB v1.0: initial public release
2024-03-30 added NUBUSPAS16-DB gerber files to readme.md
2024-04-02 KiKad 8 upgrade
2024-04-02 VIA PLCC2DIP v1.0: initial public release
2024-11-26 Update to KiKad 8
2024-11-30 removing useless files
2024-12-07 Added Applied Engineering QuadraLink v2.2 ROM (27C128)
2025-01-02 PB5xx ATXCPU v1.3: back to THT, moded to use IDC sockets
2025-02-22 SIMM72BL v1.2: fixed decoupling caps footprint & silkscreen
2025-02-25 added LC PDS connector
2025-02-25 LC PDS: make pin names visible
2025-03-11 VIA Plus 1.2: initial public release
2025-03-11 added PLD files for 16V8
2025-03-12 added VIA Plus documentation
2025-03-12 added footprint for LC PDS connector
2025-03-14 moved MacSnap SCSI to its own repo
2025-03-19 switched to CERN license
2025-03-31 PB5xx Floppy v1.2: respin adapter for use in BBRX77
2025-03-31 cleaning
2025-03-31 updated tables
2025-04-01 clearance
2025-04-13 PB5xx ATXCPU v1.4: add provisioning for small decoupling capacitor
2025-04-13 added ADB Filter symbol
2025-05-03 VIA Plus: added AF16V8BQL-15PU compatiblity
2025-05-12 added LaserWriter IIsc ROMs
2025-05-12 added Personal LaserWriter SC ROMs + missing .md5 files
2025-05-13 PB5xx ATXCPU: upgrade to KiKad 9
2025-05-17 renamed files
2025-05-17 added Personal NT ROMs
2025-05-17 renamed a few files
2025-05-27 added PIC IOP 344S1021
2025-05-28 Update README.md
    fixed typo
2025-06-03 Connector_Apple: added 8530 SCC in PLCC-44 package
2025-06-08 Connector_Apple: added 26LS32 PLCC-20
2025-08-29 added PowerBook 500 series Power Manager ROM
2025-09-20 added the Personal LaserWriter NT coprocessor ROM
2025-09-21 PICDB: added schematics from the Personal LaserWriter NT board
2025-09-24 PICDB: added README.md
2026-03-20 EDA lib: added CD40107BE
